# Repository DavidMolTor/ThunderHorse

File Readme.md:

# Thunder Horse

Desing for a combination of a flight controller and ESC for a long range 2S FPV quadcopter.

## Introduction

TODO

## Features

TODO

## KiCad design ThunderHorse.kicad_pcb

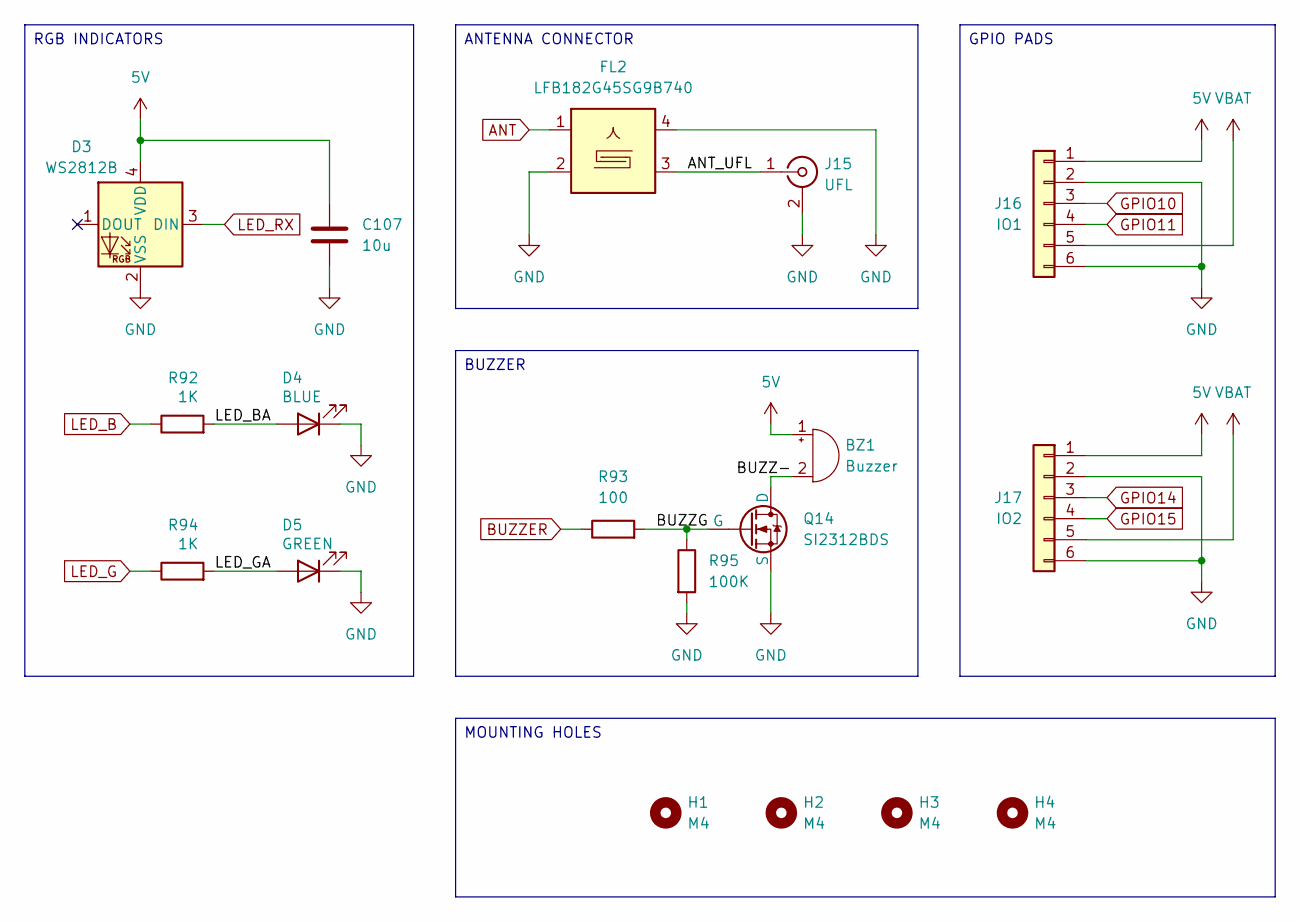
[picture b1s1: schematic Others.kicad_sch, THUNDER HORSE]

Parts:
BZ1: Buzzer; FUET_9018
C107: 10u; C_0805_2012Metric
D3: WS2812B; WS2812B-2020
D4: BLUE; LED_0603_1608Metric
D5: GREEN; LED_0603_1608Metric
FL2: LFB182G45SG9B740
H1, H2, H3, H4: M4; MOUNTING_FC_4.0mm
J15: UFL; U.FL_Hirose_U.FL-R-SMT-1_Vertical
J16: IO1; PAD_6_SQUARE_SOLID_1.5x1.5mm_P2.0mm
J17: IO2; PAD_6_SQUARE_SOLID_1.5x1.5mm_P2.0mm
Q14: SI2312BDS; SOT-23
R92, R94: 1K; R_0603_1608Metric
R93: 100; R_0603_1608Metric
R95: 100K; R_0603_1608Metric

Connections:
5V: BZ1.1 (+), C107.1, D3.4 (VDD), J16.1, J17.1; also elsewhere on the board
/Others/ANT_UFL: FL2.3, J15.1 (In)
/Others/BUZZ-: BZ1.2 (-), Q14.3 (D)
/Others/BUZZG: Q14.1 (G), R93.2, R95.1
/Others/LED_BA: D4.2 (A), R92.2
/Others/LED_GA: D5.2 (A), R94.2
ANT: FL2.1; also elsewhere on the board
BUZZER: R93.1; also elsewhere on the board
GND: C107.2, D3.2 (VSS), D4.1 (K), D5.1 (K), FL2.2, FL2.4, J15.2 (Ext), J16.2, J16.6, J17.2, J17.6, Q14.2 (S), R95.2; also elsewhere on the board
GPIO10: J16.3; also elsewhere on the board
GPIO11: J16.4; also elsewhere on the board
GPIO14: J17.3; also elsewhere on the board
GPIO15: J17.4; also elsewhere on the board
LED_B: R92.1; also elsewhere on the board
LED_G: R94.1; also elsewhere on the board
LED_RX: D3.3 (DIN); also elsewhere on the board
VBAT: J16.5, J17.5; also elsewhere on the board

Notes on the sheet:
GPIO PADS
ANTENNA CONNECTOR
MOUNTING HOLES
BUZZER
RGB INDICATORS

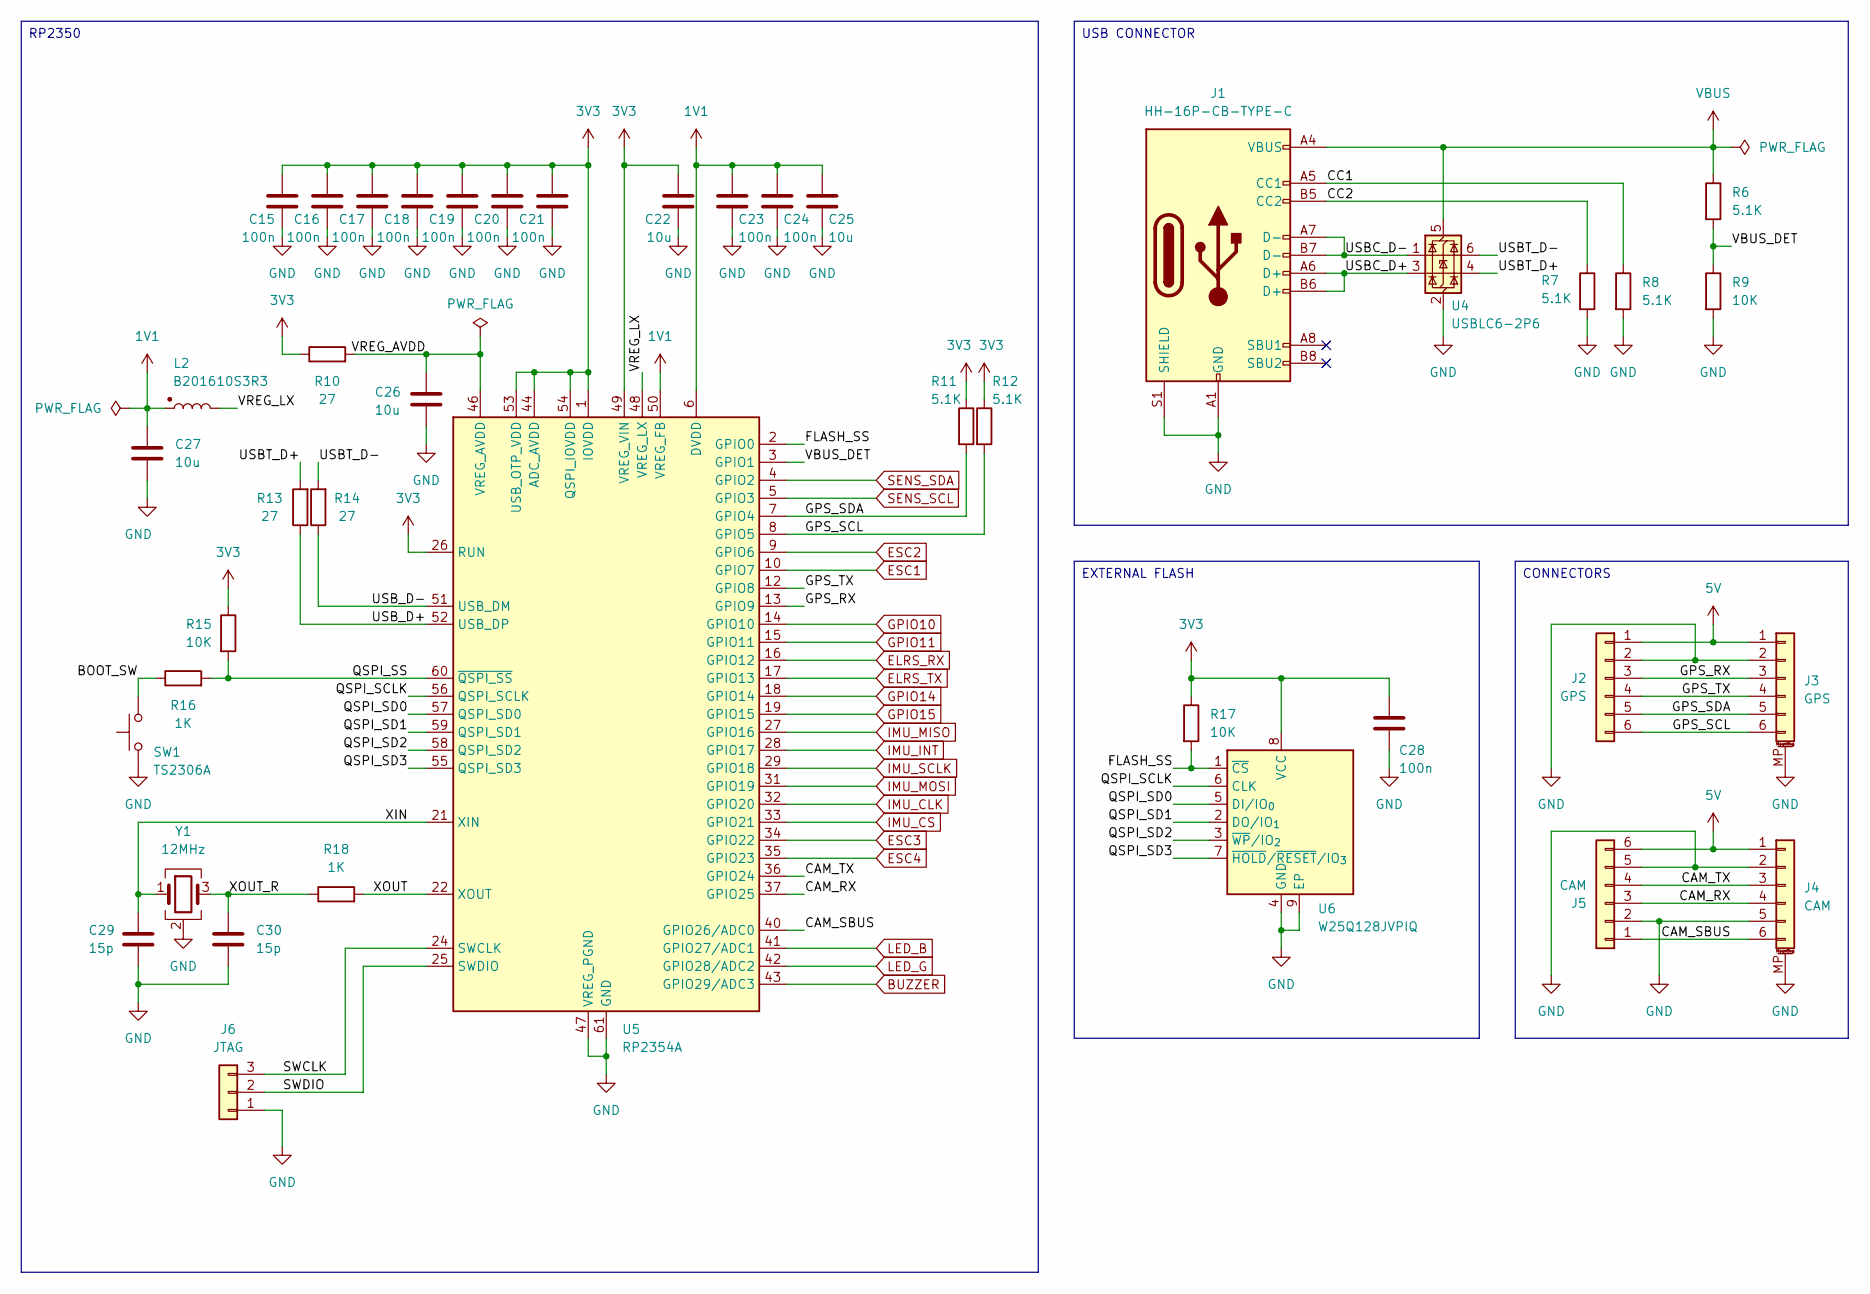
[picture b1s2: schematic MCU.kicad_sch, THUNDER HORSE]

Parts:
C15, C16, C17, C18, C19, C20, C21, C23, C24, C28: 100n; C_0603_1608Metric
C22, C25, C26, C27: 10u; C_0603_1608Metric
C29, C30: 15p; C_0603_1608Metric
J1: HH-16P-CB-TYPE-C
J2: GPS; PAD_6_SQUARE_SOLID_1.5x1.5mm_P2.0mm
J3: GPS; JST_SH_SM06B-SRSS-TB_1x06-1MP_P1.00mm_Horizontal
J4: CAM; JST_SH_SM06B-SRSS-TB_1x06-1MP_P1.00mm_Horizontal
J5: CAM; PAD_6_SQUARE_SOLID_1.5x1.5mm_P2.0mm
J6: JTAG; PAD_3_SQUARE_SOLID_1.0x1.0mm_P1.5mm
L2: B201610S3R3; AOTAB201610S3R3101T
R6, R7, R8, R11, R12: 5.1K; R_0603_1608Metric
R9, R15, R17: 10K; R_0603_1608Metric
R10, R13, R14: 27; R_0603_1608Metric
R16, R18: 1K; R_0603_1608Metric
SW1: TS2306A; SW_SMD_3.0x2.0_PUSH
U4: USBLC6-2P6; SOT-666
U5: RP2354A; RP2350A_QFN-60_EP_7.75x7.75_Pitch0.4mm
U6: W25Q128JVPIQ; WSON-8-1EP_6x5mm_P1.27mm_EP3.4x4.3mm
Y1: 12MHz; Crystal_SMD_2016-4Pin_2.0x1.6mm

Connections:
1V1: C23.1, C24.1, C25.1, C27.1, L2.1, U5.6 (DVDD), U5.23 (DVDD), U5.39 (DVDD), U5.50 (VREG_FB)
3V3: C15.1, C16.1, C17.1, C18.1, C19.1, C20.1, C21.1, C22.1, C28.1, R10.1, R11.1, R12.1, R15.1, R17.1, U5.1 (IOVDD), U5.11 (IOVDD), U5.20 (IOVDD), U5.26 (RUN), U5.30 (IOVDD), U5.38 (IOVDD), U5.44 (ADC_AVDD), U5.45 (IOVDD), U5.49 (VREG_VIN), U5.53 (USB_OTP_VDD), U5.54 (QSPI_IOVDD), U6.8 (VCC); also elsewhere on the board
5V: J2.1, J3.1, J4.1, J5.6; also elsewhere on the board
/MCU/BOOT_SW: R16.1, SW1.2
/MCU/CAM_RX: J4.4, J5.3, U5.37 (GPIO25)
/MCU/CAM_SBUS: J4.6, J5.1, U5.40 (GPIO26/ADC0)
/MCU/CAM_TX: J4.3, J5.4, U5.36 (GPIO24)
/MCU/CC1: J1.A5 (CC1), R8.1
/MCU/CC2: J1.B5 (CC2), R7.1
/MCU/FLASH_SS: R17.2, U5.2 (GPIO0), U6.1 (~CS)
/MCU/GPS_RX: J2.3, J3.3, U5.13 (GPIO9)
/MCU/GPS_SCL: J2.6, J3.6, R12.2, U5.8 (GPIO5)
/MCU/GPS_SDA: J2.5, J3.5, R11.2, U5.7 (GPIO4)
/MCU/GPS_TX: J2.4, J3.4, U5.12 (GPIO8)
/MCU/QSPI_SCLK: U5.56 (QSPI_SCLK), U6.6 (CLK)
/MCU/QSPI_SD0: U5.57 (QSPI_SD0), U6.5 (DI/IO_{0})
/MCU/QSPI_SD1: U5.59 (QSPI_SD1), U6.2 (DO/IO_{1})
/MCU/QSPI_SD2: U5.58 (QSPI_SD2), U6.3 (~WP/IO_{2})
/MCU/QSPI_SD3: U5.55 (QSPI_SD3), U6.7 (~HOLD/~RESET/IO_{3})
/MCU/QSPI_SS: R15.2, R16.2, U5.60 (~QSPI_SS)
/MCU/SWCLK: J6.3, U5.24 (SWCLK)
/MCU/SWDIO: J6.2, U5.25 (SWDIO)
/MCU/USBC_D+: J1.A6 (D+), J1.B6 (D+), U4.3 (I/O2)
/MCU/USBC_D-: J1.A7 (D-), J1.B7 (D-), U4.1 (I/O1)
/MCU/USBT_D+: R13.2, U4.4 (I/O2)
/MCU/USBT_D-: R14.2, U4.6 (I/O1)
/MCU/USB_D+: R13.1, U5.52 (USB_DP)
/MCU/USB_D-: R14.1, U5.51 (USB_DM)
/MCU/VBUS_DET: R6.2, R9.1, U5.3 (GPIO1)
/MCU/VREG_AVDD: C26.1, R10.2, U5.46 (VREG_AVDD)
/MCU/VREG_LX: L2.2, U5.48 (VREG_LX)
/MCU/XIN: C29.1, U5.21 (XIN), Y1.1
/MCU/XOUT: R18.2, U5.22 (XOUT)
/MCU/XOUT_R: C30.1, R18.1, Y1.3
BUZZER: U5.43 (GPIO29/ADC3); also elsewhere on the board
ELRS_RX: U5.16 (GPIO12); also elsewhere on the board
ELRS_TX: U5.17 (GPIO13); also elsewhere on the board
ESC1: U5.10 (GPIO7); also elsewhere on the board
ESC2: U5.9 (GPIO6); also elsewhere on the board
ESC3: U5.34 (GPIO22); also elsewhere on the board
ESC4: U5.35 (GPIO23); also elsewhere on the board
GND: C15.2, C16.2, C17.2, C18.2, C19.2, C20.2, C21.2, C22.2, C23.2, C24.2, C25.2, C26.2, C27.2, C28.2, C29.2, C30.2, J1.A1 (GND), J1.B1 (GND), J1.S1 (SHIELD), J2.2, J3.2, J3.MP (MountPin), J4.2, J4.5, J4.MP (MountPin), J5.2, J5.5, J6.1, R7.2, R8.2, R9.2, SW1.1, U4.2 (GND), U5.47 (VREG_PGND), U5.61 (GND), U6.4 (GND), U6.9 (EP), Y1.2 (G), Y1.4 (G); also elsewhere on the board
GPIO10: U5.14 (GPIO10); also elsewhere on the board
GPIO11: U5.15 (GPIO11); also elsewhere on the board
GPIO14: U5.18 (GPIO14); also elsewhere on the board
GPIO15: U5.19 (GPIO15); also elsewhere on the board
IMU_CLK: U5.32 (GPIO20); also elsewhere on the board
IMU_CS: U5.33 (GPIO21); also elsewhere on the board
IMU_INT: U5.28 (GPIO17); also elsewhere on the board
IMU_MISO: U5.27 (GPIO16); also elsewhere on the board
IMU_MOSI: U5.31 (GPIO19); also elsewhere on the board
IMU_SCLK: U5.29 (GPIO18); also elsewhere on the board
LED_B: U5.41 (GPIO27/ADC1); also elsewhere on the board
LED_G: U5.42 (GPIO28/ADC2); also elsewhere on the board
SENS_SCL: U5.5 (GPIO3); also elsewhere on the board
SENS_SDA: U5.4 (GPIO2); also elsewhere on the board
VBUS: J1.A4 (VBUS), J1.B4 (VBUS), R6.1, U4.5 (VBUS); also elsewhere on the board

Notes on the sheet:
CONNECTORS
USB CONNECTOR
EXTERNAL FLASH
RP2350

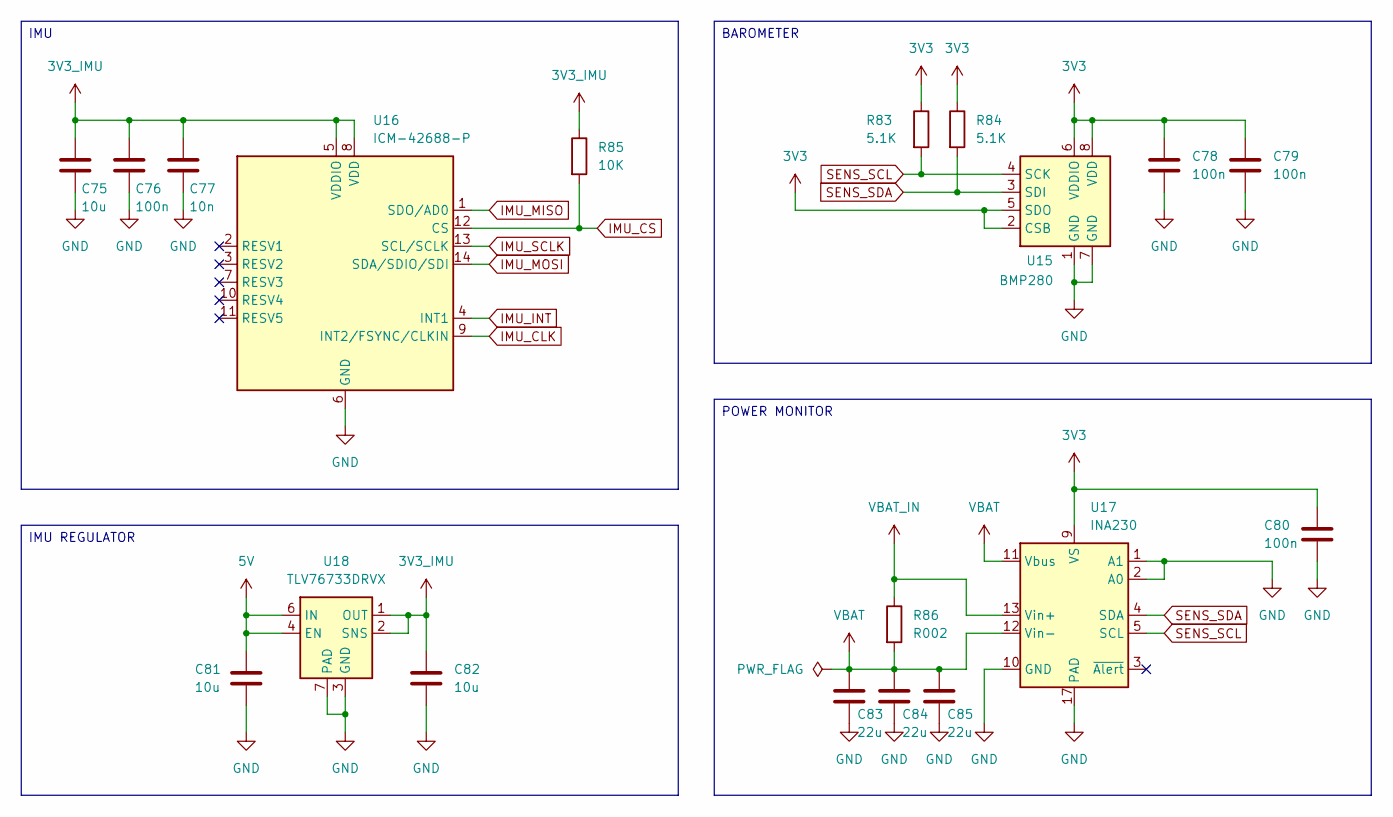
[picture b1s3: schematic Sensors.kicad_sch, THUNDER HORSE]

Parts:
C75, C81, C82: 10u; C_0805_2012Metric
C76, C78, C79, C80: 100n; C_0603_1608Metric
C77: 10n; C_0603_1608Metric
C83, C84, C85: 22u; C_1206_3216Metric
R83, R84: 5.1K; R_0603_1608Metric
R85: 10K; R_0603_1608Metric
R86: R002; R_2512_6332Metric
U15: BMP280; LGA-8_2x2.5mm_P0.65mm
U16: ICM-42688-P; Mouser Part Number 410-ICM-42688-P
U17: INA230; VQFN-16-1EP_3x3mm_P0.5mm_EP1.6x1.6mm_ThermalVias
U18: TLV76733DRVX; WSON-6-1EP_2x2mm_P0.65mm_EP1x1.6mm_ThermalVias

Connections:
3V3: C78.1, C79.1, C80.1, R83.1, R84.1, U15.2 (CSB), U15.5 (SDO), U15.6 (VDDIO), U15.8 (VDD), U17.9 (VS); also elsewhere on the board
3V3_IMU: C75.1, C76.1, C77.1, C82.1, R85.1, U16.5 (VDDIO), U16.8 (VDD), U18.1 (OUT), U18.2 (SNS)
5V: C81.1, U18.4 (EN), U18.6 (IN); also elsewhere on the board
GND: C75.2, C76.2, C77.2, C78.2, C79.2, C80.2, C81.2, C82.2, C83.2, C84.2, C85.2, U15.1 (GND), U15.7 (GND), U16.6 (GND), U17.1 (A1), U17.2 (A0), U17.10 (GND), U17.17 (PAD), U18.3 (GND), U18.5 (GND), U18.7 (PAD); also elsewhere on the board
IMU_CLK: U16.9 (INT2/FSYNC/CLKIN); also elsewhere on the board
IMU_CS: R85.2, U16.12 (CS); also elsewhere on the board
IMU_INT: U16.4 (INT1); also elsewhere on the board
IMU_MISO: U16.1 (SDO/AD0); also elsewhere on the board
IMU_MOSI: U16.14 (SDA/SDIO/SDI); also elsewhere on the board
IMU_SCLK: U16.13 (SCL/SCLK); also elsewhere on the board
SENS_SCL: R83.2, U15.4 (SCK), U17.5 (SCL); also elsewhere on the board
SENS_SDA: R84.2, U15.3 (SDI), U17.4 (SDA); also elsewhere on the board
VBAT: C83.1, C84.1, C85.1, R86.2, U17.11 (Vbus), U17.12 (Vin-); also elsewhere on the board
VBAT_IN: R86.1, U17.13 (Vin+); also elsewhere on the board

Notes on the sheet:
IMU REGULATOR
IMU
POWER MONITOR
BAROMETER

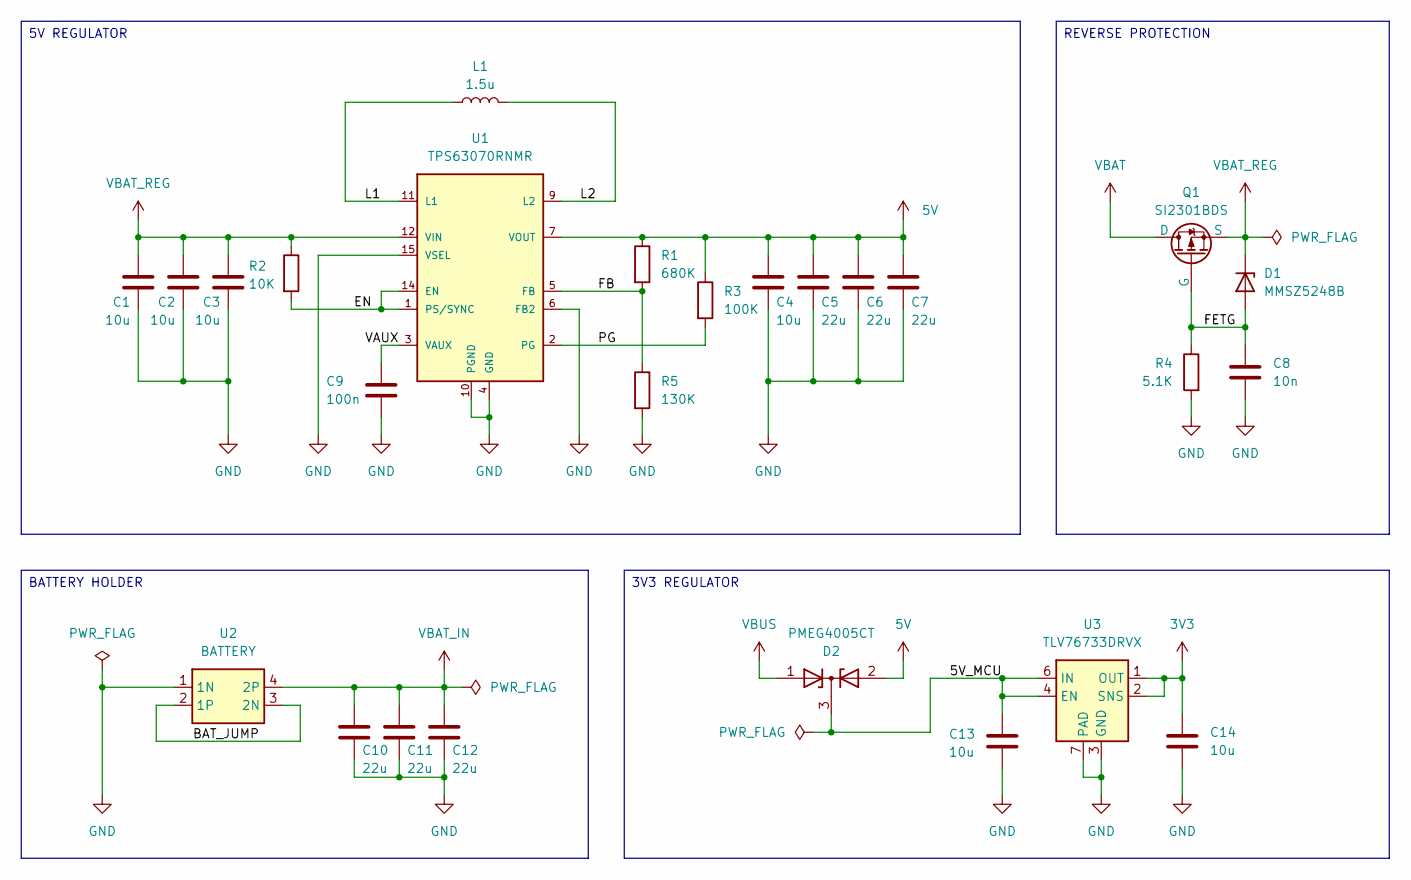
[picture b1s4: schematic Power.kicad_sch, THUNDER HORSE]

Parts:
C1, C2, C13, C14: 10u; C_0805_2012Metric
C3, C4: 10u; C_0603_1608Metric
C5, C6, C7, C10, C11, C12: 22u; C_1206_3216Metric
C8: 10n; C_0603_1608Metric
C9: 100n; C_0603_1608Metric
D1: MMSZ5248B; D_SOD-523
D2: PMEG4005CT; SOT-23
L1: 1.5u; L_Panasonic_PCC-M0530M
Q1: SI2301BDS; SOT-23
R1: 680K; R_0603_1608Metric
R2: 10K; R_0603_1608Metric
R3: 100K; R_0603_1608Metric
R4: 5.1K; R_0603_1608Metric
R5: 130K; R_0603_1608Metric
U1: TPS63070RNMR; PARTREV B
U2: BATTERY; 21700_DUAL_HOLDER_MOUNTING; Mouser Part Number 534-1048
U3: TLV76733DRVX; WSON-6-1EP_2x2mm_P0.65mm_EP1x1.6mm_ThermalVias

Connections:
3V3: C14.1, U3.1 (OUT), U3.2 (SNS); also elsewhere on the board
5V: C4.1, C5.1, C6.1, C7.1, D2.2 (A), R1.1, R3.1, U1.7 (VOUT); also elsewhere on the board
/Power/5V_MCU: C13.1, D2.3 (K), U3.4 (EN), U3.6 (IN)
/Power/BAT_JUMP: U2.2 (1P), U2.3 (2N)
/Power/EN: R2.2, U1.1 (PS/SYNC), U1.14 (EN)
/Power/FB: R1.2, R5.1, U1.5 (FB)
/Power/FETG: C8.1, D1.2 (A), Q1.1 (G), R4.1
/Power/L1: L1.1, U1.11 (L1)
/Power/L2: L1.2, U1.9 (L2)
/Power/PG: R3.2, U1.2 (PG)
/Power/VAUX: C9.1, U1.3 (VAUX)
GND: C1.2, C2.2, C3.2, C4.2, C5.2, C6.2, C7.2, C8.2, C9.2, C10.2, C11.2, C12.2, C13.2, C14.2, R4.2, R5.2, U1.4 (GND), U1.6 (FB2), U1.10 (PGND), U1.15 (VSEL), U2.1 (1N), U3.3 (GND), U3.5 (GND), U3.7 (PAD); also elsewhere on the board
VBAT: Q1.3 (D); also elsewhere on the board
VBAT_IN: C10.1, C11.1, C12.1, U2.4 (2P); also elsewhere on the board
VBAT_REG: C1.1, C2.1, C3.1, D1.1 (K), Q1.2 (S), R2.1, U1.12 (VIN)
VBUS: D2.1 (A); also elsewhere on the board

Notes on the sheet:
BATTERY HOLDER
3V3 REGULATOR
5V REGULATOR
REVERSE PROTECTION

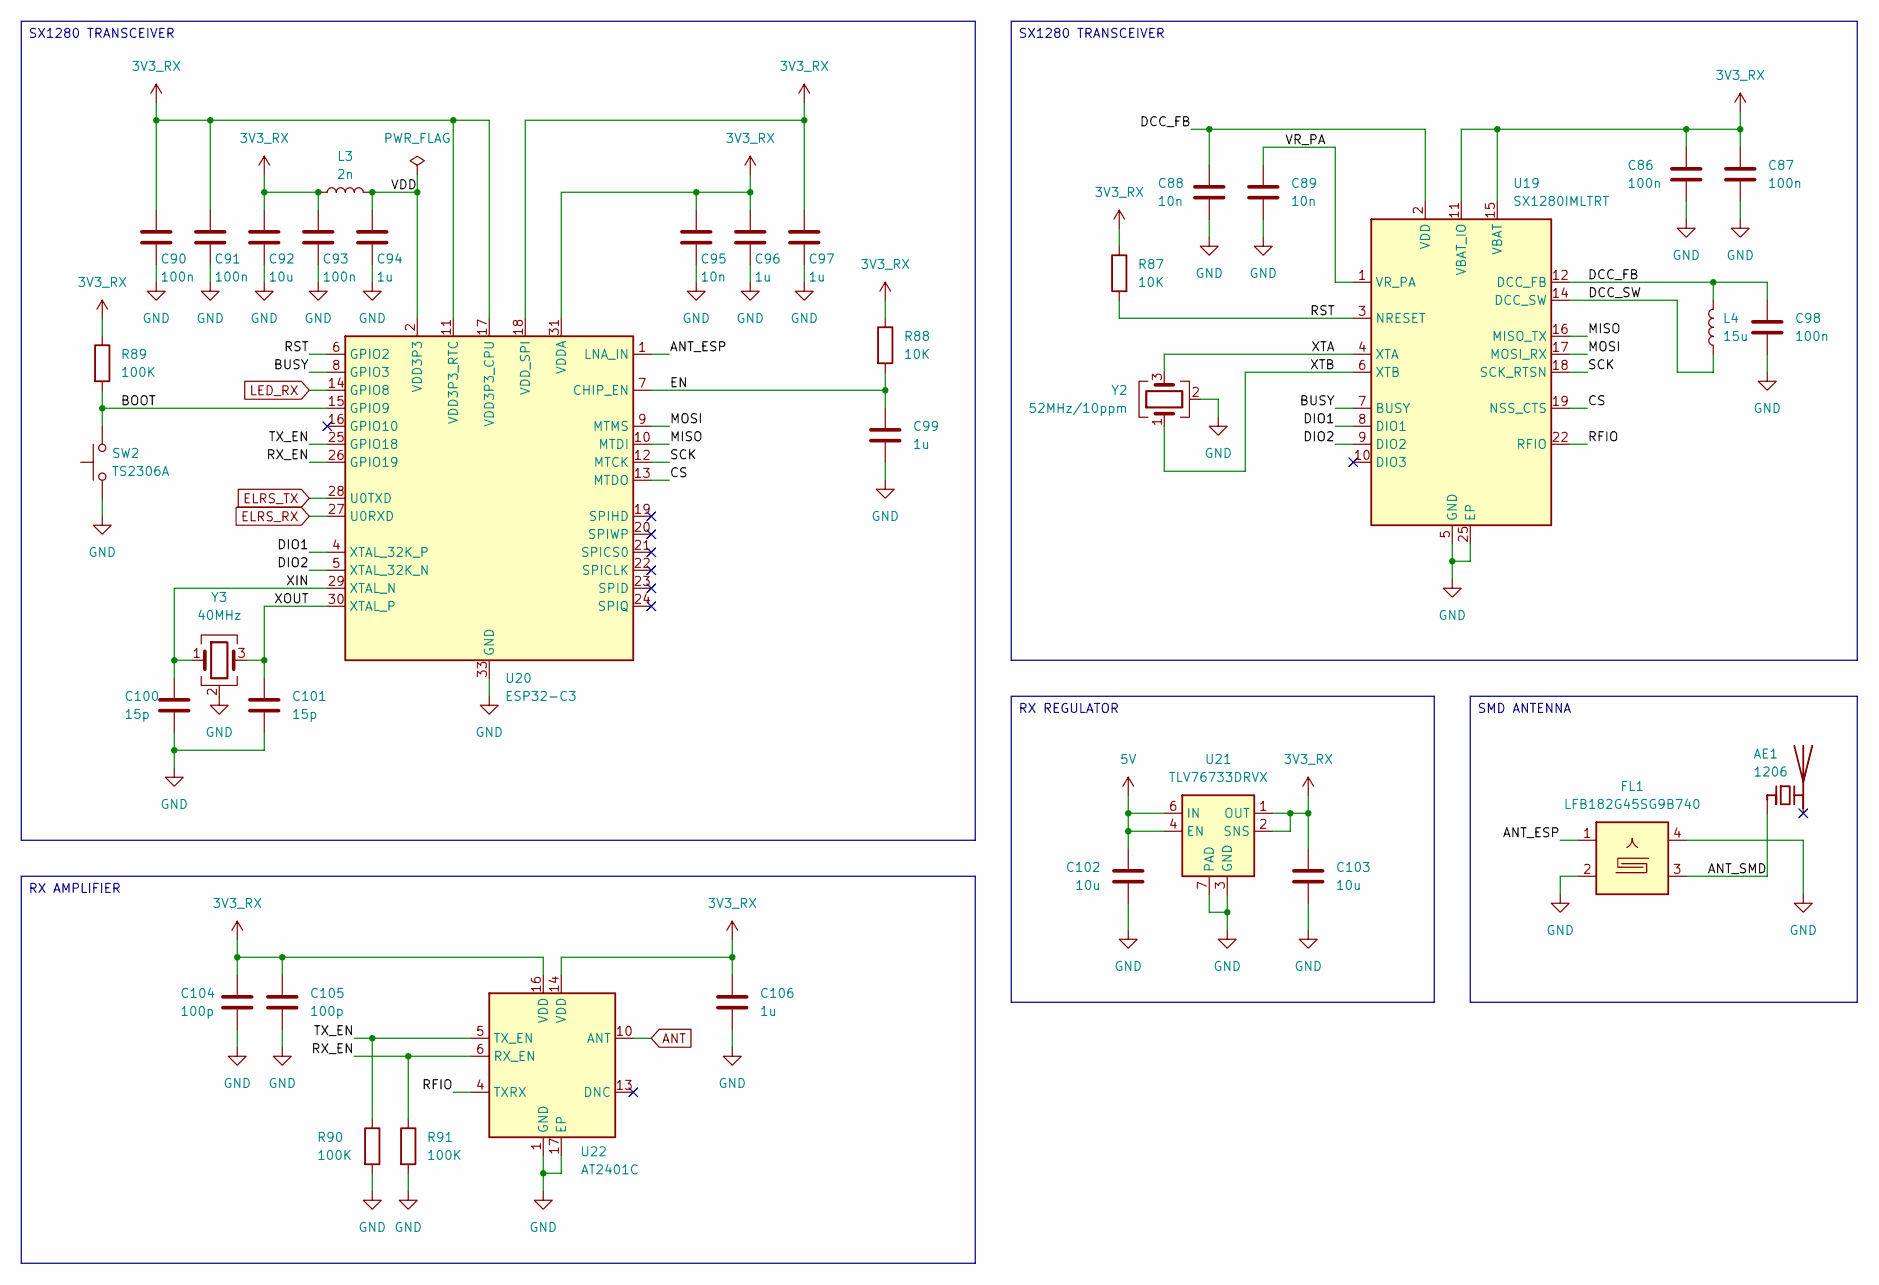
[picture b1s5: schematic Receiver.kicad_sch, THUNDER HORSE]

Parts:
AE1: 1206; L_1206_3216Metric
C86, C87, C90, C91, C93, C98: 100n; C_0603_1608Metric
C88, C89, C95: 10n; C_0603_1608Metric
C92, C102, C103: 10u; C_0805_2012Metric
C94, C96, C97, C99, C106: 1u; C_0603_1608Metric
C100, C101: 15p; C_0603_1608Metric
C104, C105: 100p; C_0603_1608Metric
FL1: LFB182G45SG9B740
L3: 2n; L_0603_1608Metric
L4: 15u; L_0603_1608Metric
R87, R88: 10K; R_0603_1608Metric
R89, R90, R91: 100K; R_0603_1608Metric
SW2: TS2306A; SW_SMD_3.0x2.0_PUSH
U19: SX1280IMLTRT; QFN-24_4x4mm_P0.5mm_EP; Mouser Part Number 947-SX1280IMLTRT
U20: ESP32-C3; QFN-32-1EP_5x5mm_P0.5mm_EP3.7x3.7mm
U21: TLV76733DRVX; WSON-6-1EP_2x2mm_P0.65mm_EP1x1.6mm_ThermalVias
U22: AT2401C; QFN-16_3x3mm_P0.5mm_EP1.7x1.7mm_EP
Y2: 52MHz/10ppm; Crystal_SMD_2016-4Pin_2.0x1.6mm
Y3: 40MHz; Crystal_SMD_2016-4Pin_2.0x1.6mm

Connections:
3V3_RX: C86.1, C87.1, C90.1, C91.1, C92.1, C93.1, C95.1, C96.1, C97.1, C103.1, C104.1, C105.1, C106.1, L3.1, R87.1, R88.1, R89.1, U19.11 (VBAT_IO), U19.15 (VBAT), U20.11 (VDD3P3_RTC), U20.17 (VDD3P3_CPU), U20.18 (VDD_SPI), U20.31 (VDDA), U20.32 (VDDA), U21.1 (OUT), U21.2 (SNS), U22.14 (VDD), U22.16 (VDD)
5V: C102.1, U21.4 (EN), U21.6 (IN); also elsewhere on the board
/Receiver/ANT_ESP: FL1.1, U20.1 (LNA_IN)
/Receiver/ANT_SMD: AE1.1 (FEED), FL1.3
/Receiver/BOOT: R89.2, SW2.2, U20.15 (GPIO9)
/Receiver/BUSY: U19.7 (BUSY), U20.8 (GPIO3)
/Receiver/CS: U19.19 (NSS_CTS), U20.13 (MTDO)
/Receiver/DCC_FB: C88.1, C98.1, L4.2, U19.2 (VDD), U19.12 (DCC_FB)
/Receiver/DCC_SW: L4.1, U19.14 (DCC_SW)
/Receiver/DIO1: U19.8 (DIO1), U20.4 (XTAL_32K_P)
/Receiver/DIO2: U19.9 (DIO2), U20.5 (XTAL_32K_N)
/Receiver/EN: C99.1, R88.2, U20.7 (CHIP_EN)
/Receiver/MISO: U19.16 (MISO_TX), U20.10 (MTDI)
/Receiver/MOSI: U19.17 (MOSI_RX), U20.9 (MTMS)
/Receiver/RFIO: U19.22 (RFIO), U22.4 (TXRX)
/Receiver/RST: R87.2, U19.3 (NRESET), U20.6 (GPIO2)
/Receiver/RX_EN: R91.1, U20.26 (GPIO19), U22.6 (RX_EN)
/Receiver/SCK: U19.18 (SCK_RTSN), U20.12 (MTCK)
/Receiver/TX_EN: R90.1, U20.25 (GPIO18), U22.5 (TX_EN)
/Receiver/VDD: C94.1, L3.2, U20.2 (VDD3P3), U20.3 (VDD3P3)
/Receiver/VR_PA: C89.1, U19.1 (VR_PA)
/Receiver/XIN: C100.1, U20.29 (XTAL_N), Y3.1
/Receiver/XOUT: C101.1, U20.30 (XTAL_P), Y3.3
/Receiver/XTA: U19.4 (XTA), Y2.3
/Receiver/XTB: U19.6 (XTB), Y2.1
ANT: U22.10 (ANT); also elsewhere on the board
ELRS_RX: U20.27 (U0RXD); also elsewhere on the board
ELRS_TX: U20.28 (U0TXD); also elsewhere on the board
GND: C86.2, C87.2, C88.2, C89.2, C90.2, C91.2, C92.2, C93.2, C94.2, C95.2, C96.2, C97.2, C98.2, C99.2, C100.2, C101.2, C102.2, C103.2, C104.2, C105.2, C106.2, FL1.2, FL1.4, R90.2, R91.2, SW2.1, U19.5 (GND), U19.13 (GND), U19.20 (GND), U19.21 (GND), U19.23 (GND), U19.24 (GND), U19.25 (EP), U20.33 (GND), U21.3 (GND), U21.5 (GND), U21.7 (PAD), U22.1 (GND), U22.2 (GND), U22.3 (GND), U22.7 (GND), U22.8 (GND), U22.9 (GND), U22.11 (GND), U22.12 (GND), U22.15 (GND), U22.17 (EP), Y2.2 (G), Y2.4 (G), Y3.2 (G), Y3.4 (G); also elsewhere on the board
LED_RX: U20.14 (GPIO8); also elsewhere on the board

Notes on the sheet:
SMD ANTENNA
SX1280 TRANSCEIVER
RX AMPLIFIER
RX REGULATOR

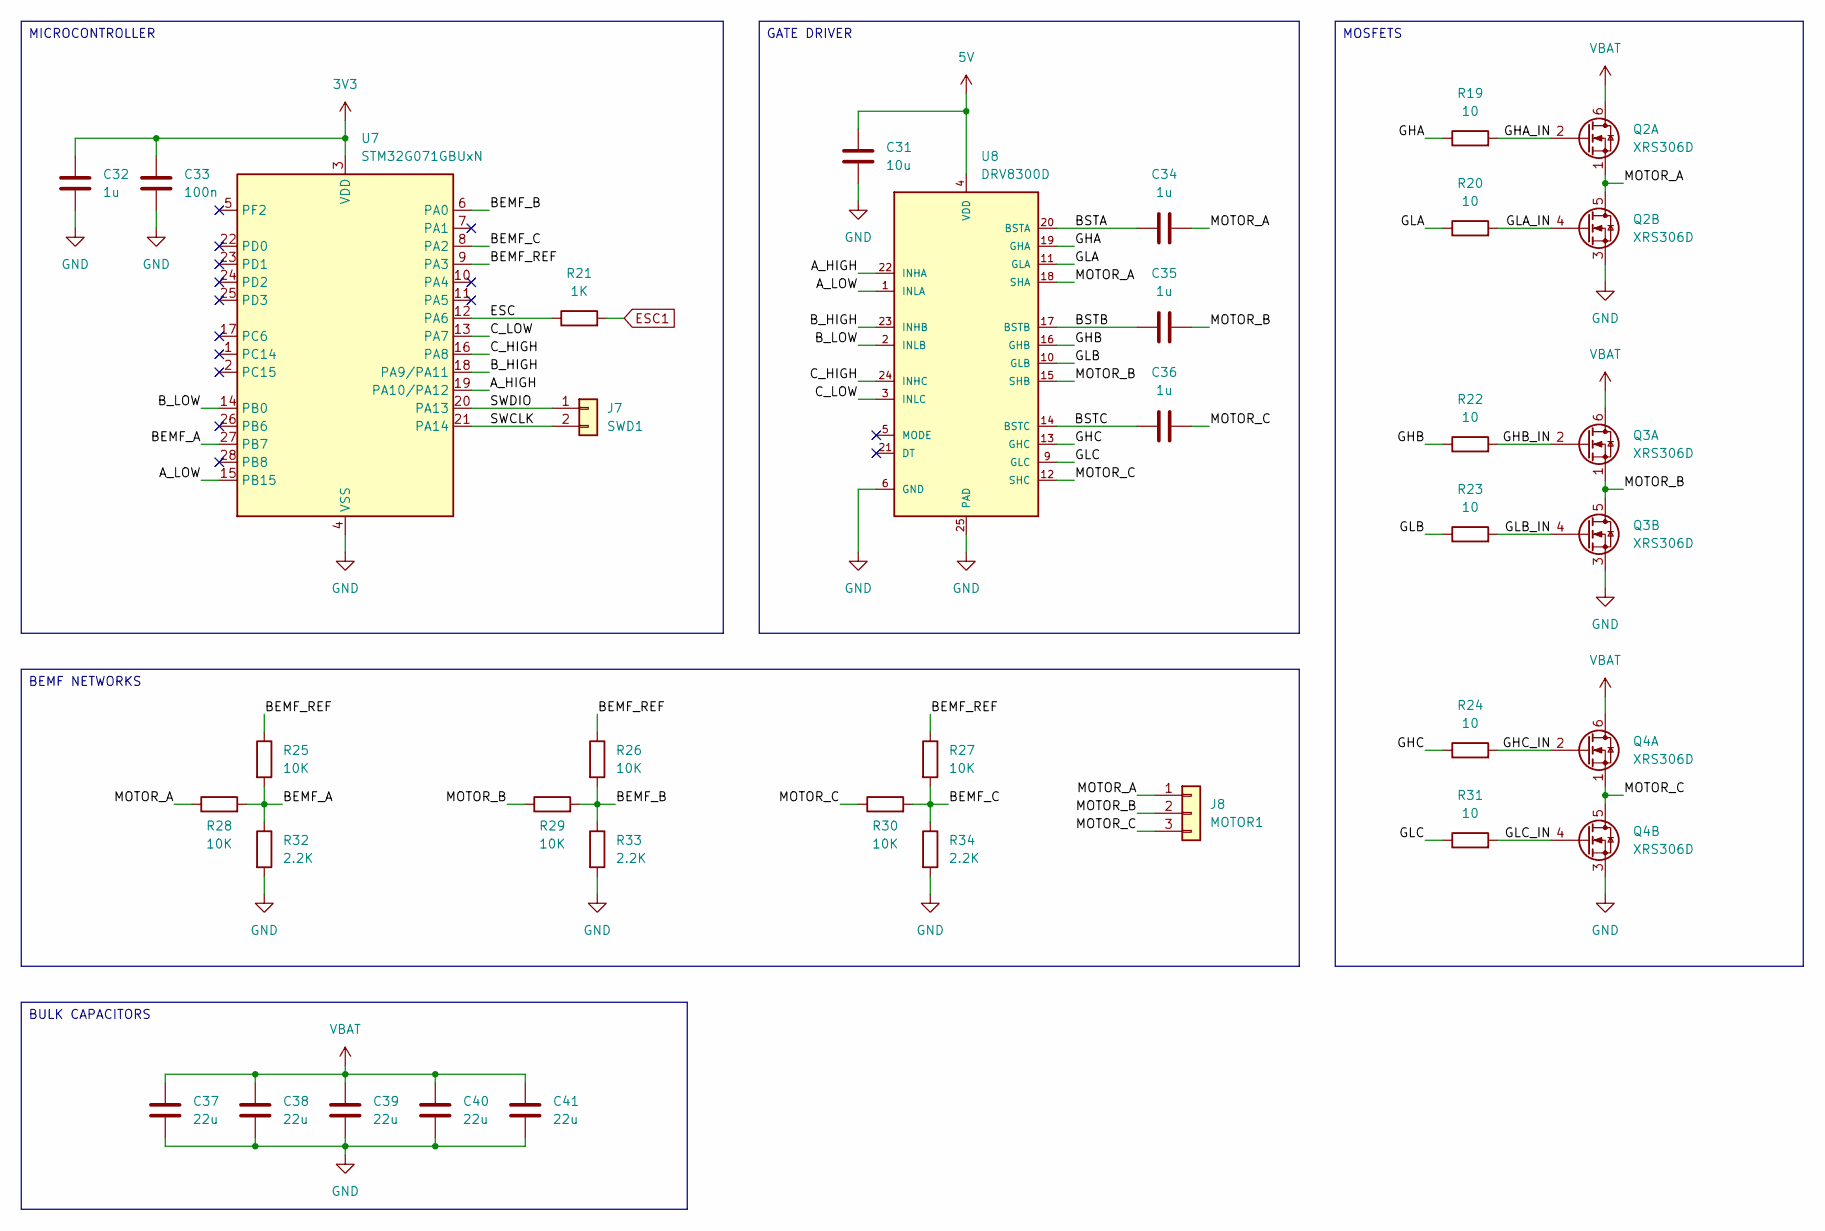
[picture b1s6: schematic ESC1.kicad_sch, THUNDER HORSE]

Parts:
C31: 10u; C_0603_1608Metric
C32, C34, C35, C36: 1u; C_0603_1608Metric
C33: 100n; C_0603_1608Metric
C37, C38, C39, C40, C41: 22u; C_1206_3216Metric
J7: SWD1; PAD_2_SQUARE_SOLID_1.0x1.0mm_P1.5mm
J8: MOTOR1; PAD_3_SQUARE_SOLID_2.5x2.5mm_P4.0mm_MOTOR
Q2, Q3, Q4: XRS306D; PDFN8_DUAL_3.3x3.3mm
R19, R20, R22, R23, R24, R31: 10; R_0603_1608Metric
R21: 1K; R_0603_1608Metric
R25, R26, R27, R28, R29, R30: 10K; R_0603_1608Metric
R32, R33, R34: 2.2K; R_0603_1608Metric
U7: STM32G071GBUxN; QFN-28_4x4mm_P0.5mm
U8: DRV8300D; VQFN-24-1EP_4x4mm_P0.5mm_EP2.45x2.45mm

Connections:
3V3: C32.1, C33.1, U7.3 (VDD); also elsewhere on the board
5V: C31.1, U8.4 (VDD); also elsewhere on the board
/ESC/ESC1/A_HIGH: U7.19 (PA10/PA12), U8.22 (INHA)
/ESC/ESC1/A_LOW: U7.15 (PB15), U8.1 (INLA)
/ESC/ESC1/BEMF_A: R25.2, R28.2, R32.1, U7.27 (PB7)
/ESC/ESC1/BEMF_B: R26.2, R29.2, R33.1, U7.6 (PA0)
/ESC/ESC1/BEMF_C: R27.2, R30.2, R34.1, U7.8 (PA2)
/ESC/ESC1/BEMF_REF: R25.1, R26.1, R27.1, U7.9 (PA3)
/ESC/ESC1/BSTA: C34.1, U8.20 (BSTA)
/ESC/ESC1/BSTB: C35.1, U8.17 (BSTB)
/ESC/ESC1/BSTC: C36.1, U8.14 (BSTC)
/ESC/ESC1/B_HIGH: U7.18 (PA9/PA11), U8.23 (INHB)
/ESC/ESC1/B_LOW: U7.14 (PB0), U8.2 (INLB)
/ESC/ESC1/C_HIGH: U7.16 (PA8), U8.24 (INHC)
/ESC/ESC1/C_LOW: U7.13 (PA7), U8.3 (INLC)
/ESC/ESC1/ESC: R21.1, U7.12 (PA6)
/ESC/ESC1/GHA: R19.1, U8.19 (GHA)
/ESC/ESC1/GHA_IN: Q2.2 (G), R19.2
/ESC/ESC1/GHB: R22.1, U8.16 (GHB)
/ESC/ESC1/GHB_IN: Q3.2 (G), R22.2
/ESC/ESC1/GHC: R24.1, U8.13 (GHC)
/ESC/ESC1/GHC_IN: Q4.2 (G), R24.2
/ESC/ESC1/GLA: R20.1, U8.11 (GLA)
/ESC/ESC1/GLA_IN: Q2.4 (G), R20.2
/ESC/ESC1/GLB: R23.1, U8.10 (GLB)
/ESC/ESC1/GLB_IN: Q3.4 (G), R23.2
/ESC/ESC1/GLC: R31.1, U8.9 (GLC)
/ESC/ESC1/GLC_IN: Q4.4 (G), R31.2
/ESC/ESC1/MOTOR_A: C34.2, J8.1, Q2.1 (S), Q2.5 (D), R28.1, U8.18 (SHA)
/ESC/ESC1/MOTOR_B: C35.2, J8.2, Q3.1 (S), Q3.5 (D), R29.1, U8.15 (SHB)
/ESC/ESC1/MOTOR_C: C36.2, J8.3, Q4.1 (S), Q4.5 (D), R30.1, U8.12 (SHC)
/ESC/ESC1/SWCLK: J7.2, U7.21 (PA14)
/ESC/ESC1/SWDIO: J7.1, U7.20 (PA13)
ESC1: R21.2; also elsewhere on the board
GND: C31.2, C32.2, C33.2, C37.2, C38.2, C39.2, C40.2, C41.2, Q2.3 (S), Q3.3 (S), Q4.3 (S), R32.2, R33.2, R34.2, U7.4 (VSS), U8.6 (GND), U8.25 (PAD); also elsewhere on the board
VBAT: C37.1, C38.1, C39.1, C40.1, C41.1, Q2.6 (D), Q3.6 (D), Q4.6 (D); also elsewhere on the board

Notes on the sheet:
GATE DRIVER
BEMF NETWORKS
MICROCONTROLLER
MOSFETS
BULK CAPACITORS
